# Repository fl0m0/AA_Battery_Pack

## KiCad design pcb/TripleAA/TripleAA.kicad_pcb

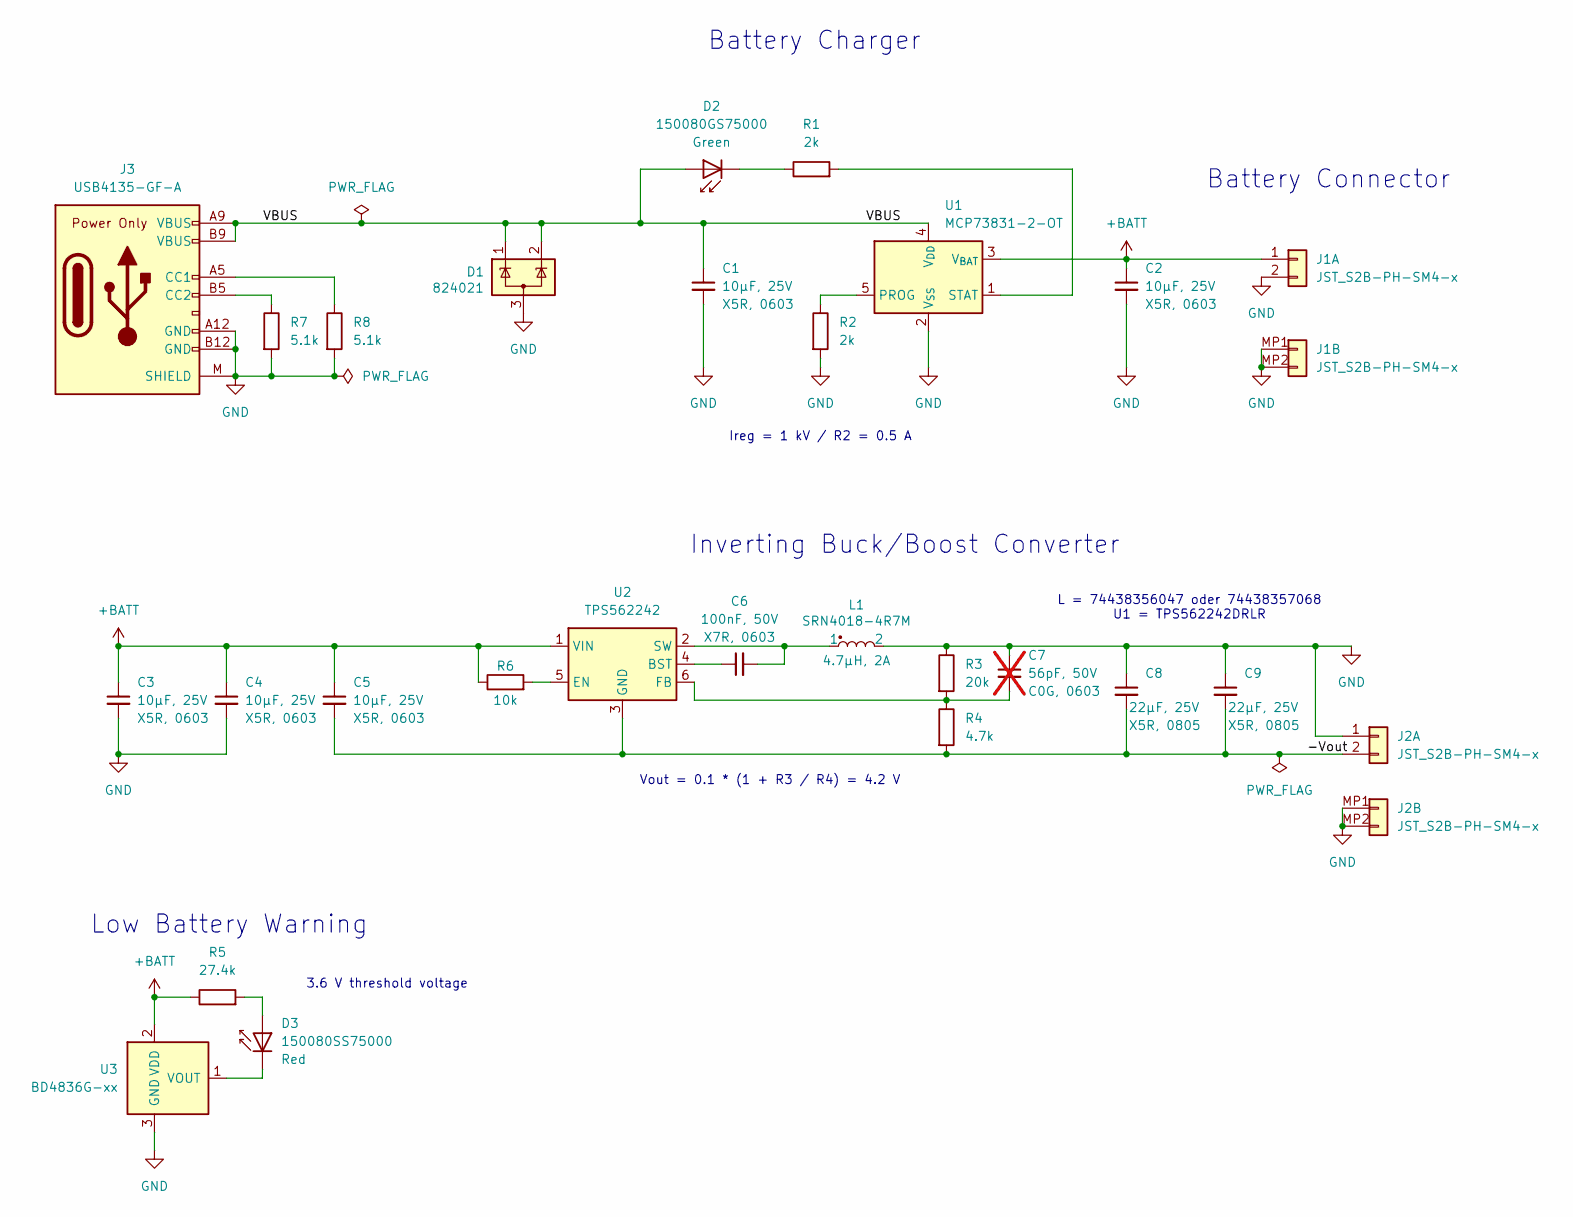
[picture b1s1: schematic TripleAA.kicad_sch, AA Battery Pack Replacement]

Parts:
C1, C2, C3, C4, C5: 10uF,25V,X5R,0603; C_0603_1608Metric_Pad1.08x0.95mm_HandSolder
C6: 100nF,50V,X7R,0603; C_0603_1608Metric_Pad1.08x0.95mm_HandSolder
C7: 56pF,50V,C0G,0603; C_0603_1608Metric_Pad1.08x0.95mm_HandSolder; not fitted
C8, C9: 22uF,25V,X5R,0805; C_0805_2012Metric_Pad1.18x1.45mm_HandSolder
D1: 824021; SOT-23_Handsoldering
D2: 150080GS75000; LED_0805_2012Metric_Pad1.15x1.40mm_HandSolder
D3: 150080SS75000; LED_0805_2012Metric_Pad1.15x1.40mm_HandSolder
J1, J2: JST_S2B-PH-SM4-x; JST_PH_S2B-PH-SM4-TB_1x02-1MP_P2.00mm_Horizontal; MPN S2B-PH-SM4-TB
J3: USB4135-GF-A; USB-C_Receptacle_GTC_USB4135-GF-A; MPN USB4135-GF-A
L1: SRN4018-4R7M; L_Bourns-SRN4018; MPN SRN4018-4R7M
R1, R2: 2k,0603; R_0603_1608Metric_Pad0.98x0.95mm_HandSolder; Tolerance 1%
R3: 20k,0603; R_0603_1608Metric_Pad0.98x0.95mm_HandSolder; Tolerance 1%
R4: 4.7k,0603; R_0603_1608Metric_Pad0.98x0.95mm_HandSolder; Tolerance 1%
R5: 27.4k,0603; R_0603_1608Metric_Pad0.98x0.95mm_HandSolder; Tolerance 1%
R6: 10k,0603; R_0603_1608Metric_Pad0.98x0.95mm_HandSolder; Tolerance 1%
R7, R8: 5.1k,0603; R_0603_1608Metric_Pad0.98x0.95mm_HandSolder; Tolerance 1%
U1: MCP73831-2-OT; SOT-23-5
U2: TPS562242; SOT-563; MPN TPS562242DRLR
U3: BD4836G-xx; SOT-23-5; MPN BD4836G-xx

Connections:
+BATT: C2.1, C3.1, C4.1, C5.1, J1.1, R5.1, R6.1, U1.3 (V_{BAT}), U2.1 (VIN), U3.2 (VDD)
/-Vout: C5.2, C8.2, C9.2, J2.2, R4.2, U2.3 (GND)
/VBUS: C1.1, D1.1 (K), D1.2 (K), D2.2 (A), J3.A9 (VBUS), J3.B9 (VBUS), U1.4 (V_{DD})
GND: C1.2, C2.2, C3.2, C4.2, C7.1, C8.1, C9.1, D1.3 (A), J1.2, J1.MP1 (MP), J1.MP2 (MP), J2.1, J2.MP1 (MP), J2.MP2 (MP), J3.A12 (GND), J3.B12 (GND), J3.M (SHIELD), L1.2, R2.2, R3.1, R7.2, R8.2, U1.2 (V_{SS}), U3.3 (GND)
unnamed: D2.1 (K), R1.1
unnamed: D3.2 (A), R5.2
unnamed: D3.1 (K), U3.1 (VOUT)
unnamed: J3.A5 (CC1), R8.1
unnamed: J3.B5 (CC2), R7.1
unnamed: R2.1, U1.5 (PROG)
unnamed: R1.2, U1.1 (STAT)
unnamed: C6.1, U2.4 (BST)
unnamed: R6.2, U2.5 (EN)
unnamed: C7.2, R3.2, R4.1, U2.6 (FB)
unnamed: C6.2, L1.1, U2.2 (SW)

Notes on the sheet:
Vout = 0.1 * (1 + R3 / R4) = 4.2 V
Battery Connector
Ireg = 1 kV / R2 = 0.5 A
L = 74438356047 oder 74438357068 U1 = TPS562242DRLR
Inverting Buck/Boost Converter
3.6 V threshold voltage
Battery Charger
Low Battery Warning

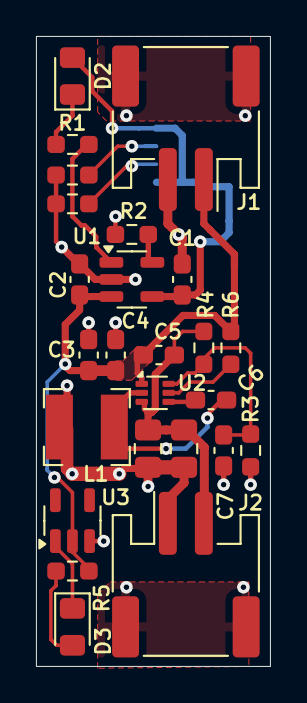
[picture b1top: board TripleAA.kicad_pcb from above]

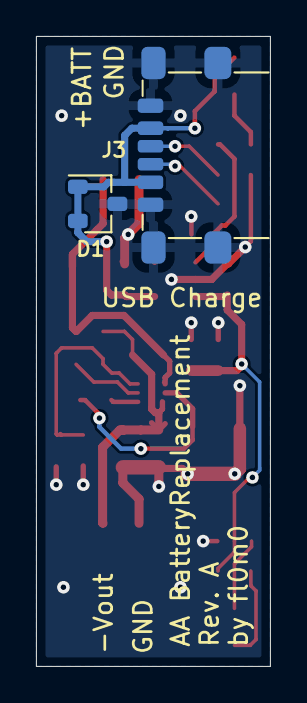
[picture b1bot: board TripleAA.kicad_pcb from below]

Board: 2 copper layers, 13.0 x 35.0 mm, 27 parts (2 on the bottom side), 15 nets.

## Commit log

2024-11-11 Add components
2024-11-13 Update SCH and PCB
2024-11-29 Finalize PCB layout
2024-11-30 Add USB connector
2024-12-01 RevA
2025-02-15 Add documentation
2025-02-15 Update mechanics
